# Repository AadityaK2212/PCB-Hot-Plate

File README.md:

# PCB-Hot-Plate
PCB hot plate. It' a hot plate for reflow sodering, but its a PCB. It works by moving a lot of current through the long copper trace, and heating it up. I needed something to solder with anyways, and when I searched it up, hot plate reflow soldering seemed the easiest, so I built my own Hot plate. It uses standoffs so as to not burn the table, but they arn't shown here

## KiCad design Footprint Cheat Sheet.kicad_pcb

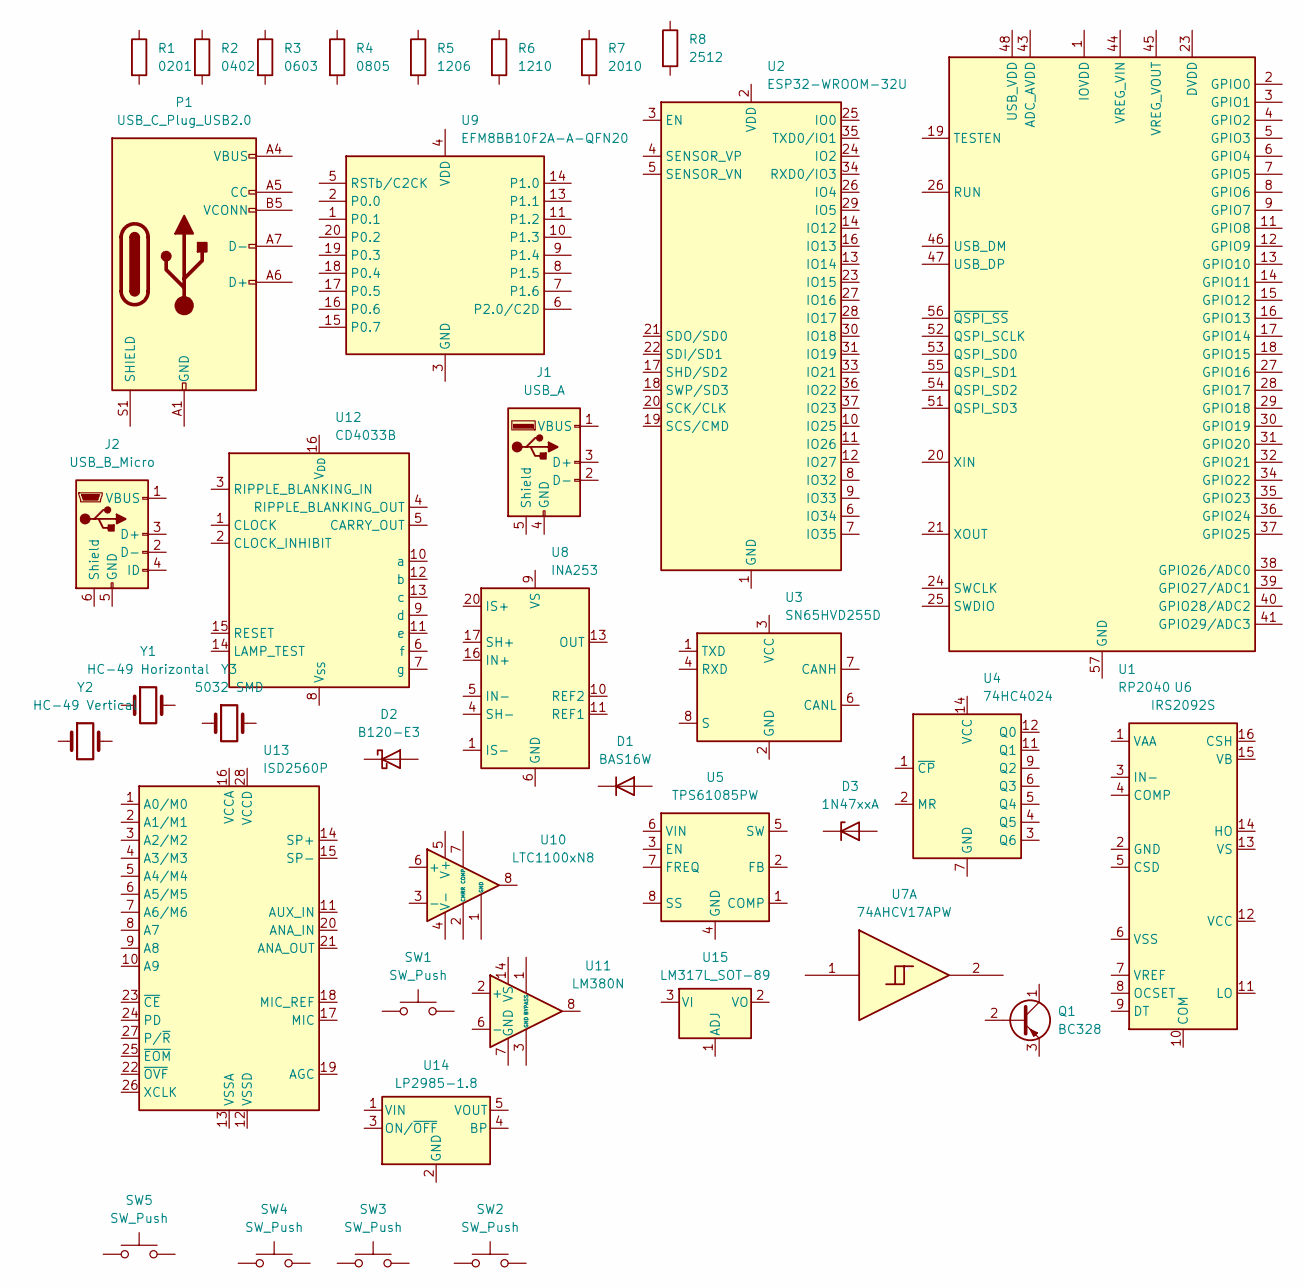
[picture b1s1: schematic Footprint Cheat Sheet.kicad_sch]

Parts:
D1: BAS16W; SOT-323_SC-70
D2: B120-E3; D_SMA
D3: 1N47xxA; D_DO-41_SOD81_P10.16mm_Horizontal
J1: USB_A; USB3_A_Molex_48393-001
J2: USB_B_Micro; USB_B_Amphenol_MUSB-D511_Vertical_Rugged
P1: USB_C_Plug_USB2.0; USB_C_Plug_Molex_105444
Q1: BC328; TO-92_Inline
R1: 0201; R_0402_1005Metric
R2: 0402; R_0201_0603Metric
R3: 0603; R_0201_0603Metric
R4: 0805; R_0805_2012Metric_Pad1.20x1.40mm_HandSolder
R5: 1206; R_1206_3216Metric_Pad1.30x1.75mm_HandSolder
R6: 1210; R_1210_3225Metric_Pad1.30x2.65mm_HandSolder
R7: 2010; R_2010_5025Metric
R8: 2512; R_2512_6332Metric
SW1: SW_Push; SW_Push_1P1T_NO_CK_KMR2
SW2: SW_Push; SW_Push_1P1T_NO_CK_KSC6xxG
SW3: SW_Push; SW_Push_1P1T_NO_CK_KSC6xxJ
SW4, SW5: SW_Push; SW_Push_1P1T_NO_CK_KSC7xxJ
U1: RP2040; QFN-56-1EP_7x7mm_P0.4mm_EP3.2x3.2mm
U2: ESP32-WROOM-32U
U3: SN65HVD255D; SOIC-8_3.9x4.9mm_P1.27mm
U4: 74HC4024; SOIC-14_3.9x8.7mm_P1.27mm
U5: TPS61085PW; TSSOP-8_4.4x3mm_P0.65mm
U6: IRS2092S; SOIC-16_3.9x9.9mm_P1.27mm
U7: 74AHCV17APW; TSSOP-14_4.4x5mm_P0.65mm
U8: INA253; TSSOP-20_4.4x6.5mm_P0.65mm
U9: EFM8BB10F2A-A-QFN20; SiliconLabs_QFN-20-1EP_3x3mm_P0.5mm_EP1.8x1.8mm
U10: LTC1100xN8; DIP-8_W7.62mm
U11: LM380N; DIP-14_W7.62mm
U12: CD4033B; DIP-16_W7.62mm
U13: ISD2560P; DIP-28_W15.24mm
U14: LP2985-1.8; SOT-23-5
U15: LM317L_SOT-89; SOT-89-3
Y1: HC-49 Horizontal; Crystal_HC49-U_Horizontal
Y2: HC-49 Vertical; Crystal_HC49-4H_Vertical
Y3: 5032 SMD; Crystal_SMD_5032-2Pin_5.0x3.2mm

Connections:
unnamed: P1.A1 (GND), P1.A12 (GND), P1.B1 (GND), P1.B12 (GND)
unnamed: P1.A4 (VBUS), P1.A9 (VBUS), P1.B4 (VBUS), P1.B9 (VBUS)
unnamed: U1.23 (DVDD), U1.50 (DVDD)
unnamed: U1.1 (IOVDD), U1.10 (IOVDD), U1.22 (IOVDD), U1.33 (IOVDD), U1.42 (IOVDD), U1.49 (IOVDD)
unnamed: U2.1 (GND), U2.15 (GND), U2.38 (GND), U2.39 (GND)
unnamed: U8.6 (GND), U8.15 (GND)
unnamed: U8.18 (IS+), U8.19 (IS+), U8.20 (IS+)
unnamed: U8.1 (IS-), U8.2 (IS-), U8.3 (IS-)
unnamed: U9.3 (GND), U9.12 (GND), U9.21 (GND)
unnamed: U11.3 (GND), U11.4 (GND), U11.5 (GND), U11.10 (GND), U11.11 (GND), U11.12 (GND)

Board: 2 copper layers, 38 parts (0 on the bottom side), 10 nets, no tracks yet.

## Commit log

2026-04-30 Add images to README for PCB hot plate
2026-04-30 Enhance README with detailed PCB hot plate description
    Expanded description of the PCB hot plate functionality and construction.
